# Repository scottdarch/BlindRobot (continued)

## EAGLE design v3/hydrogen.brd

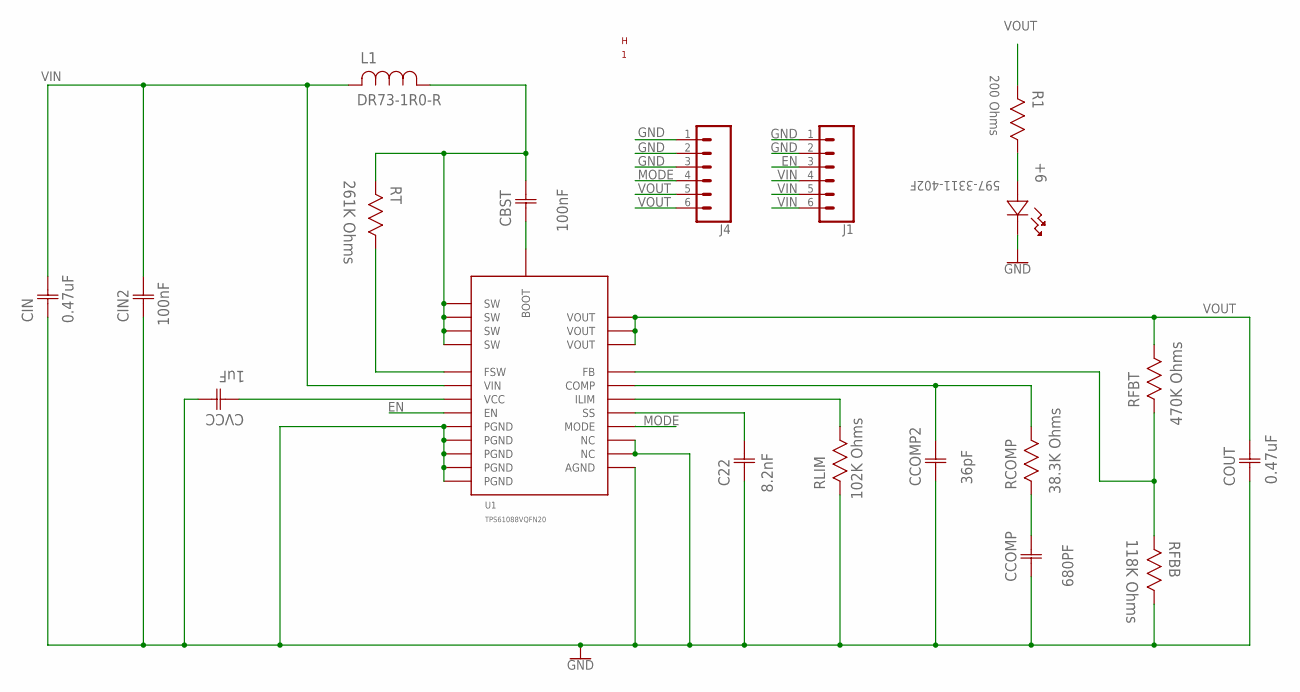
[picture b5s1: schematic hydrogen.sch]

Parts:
+6: 597-3311-402F; LED_597-3311-402F
C22: 8.2nF; CAPC1005X60N
CBST: 100nF; CAPC2013X94N
CCOMP: 680PF; CAPC1608X90N
CCOMP2: 36pF; CAPC1005X60N
CIN: 0.47uF; CAPC3216X180N
CIN2: 100nF; CAPC1005X60N
COUT: 0.47uF; CAPC3216X180N
CVCC: 1uF; CAPC1608X85N
H: 1; PERIODIC_SYMBOL_BACK
J1, J4: CONN_06LONGPADS; 1X06_LONGPADS
L1: DR73-1R0-R; INDM7676X355N
R1: 200 Ohms; RESC3216X71N
RCOMP: 38.3K Ohms; RESC1005X40N
RFBB: 118K Ohms; RESC1005X40N
RFBT: 470K Ohms; RESC1608X60N
RLIM: 102K Ohms; RESC1005X40N
RT: 261K Ohms; RESC1005X40N
U1: TPS61088VQFN20; VQFN20

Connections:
BOOT: CBST.1 (C1), U1.P$8 (BOOT)
COMP: CCOMP2.2 (C2), RCOMP.1, U1.P$18 (COMP)
EN: J1.3, U1.P$2 (EN)
FB: RFBB.2, RFBT.2 (R2), U1.P$17 (FB)
FSW: RT.1, U1.P$3 (FSW)
GND: +6.1, C22.1 (C1), CCOMP.1 (C1), CCOMP2.1 (C1), CIN.1 (C1), CIN2.1 (C1), COUT.1 (C1), CVCC.2 (C2), J1.1 (>NAME), J1.2, J4.1 (>NAME), J4.2, J4.3, RFBB.1, RLIM.2, U1.P$11 (NC), U1.P$12 (NC), U1.P$20 (AGND), U1.P$21 (PGND), U1.P$22 (PGND), U1.P$23 (PGND), U1.P$24 (PGND), U1.P$25 (PGND)
ILIM: RLIM.1, U1.P$19 (ILIM)
LED_ANODE: +6.2, R1.1
MODE: J4.4, U1.P$13 (MODE)
unnamed: CCOMP.2 (C2), RCOMP.2
SS: C22.2 (C2), U1.P$10 (SS)
SW: CBST.2 (C2), L1.1, RT.2, U1.P$4 (SW), U1.P$5 (SW), U1.P$6 (SW), U1.P$7 (SW)
VCC: CVCC.1 (C1), U1.P$1 (VCC)
VIN: CIN.2 (C2), CIN2.2 (C2), J1.4, J1.5, J1.6, L1.2, U1.P$9 (VIN)
VOUT: COUT.2 (C2), J4.5, J4.6, R1.2, RFBT.1 (R1), U1.P$14 (VOUT), U1.P$15 (VOUT), U1.P$16 (VOUT)

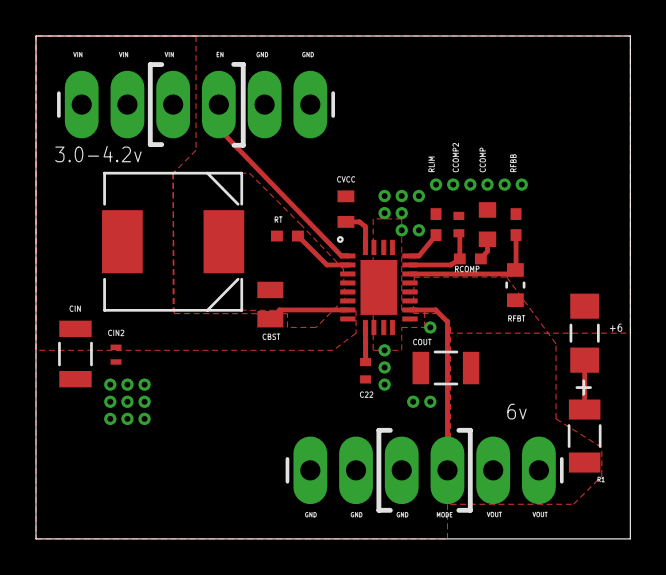
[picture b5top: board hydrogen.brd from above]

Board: 2 copper layers, 33.0 x 27.9 mm, 20 parts (0 on the bottom side), 15 nets.

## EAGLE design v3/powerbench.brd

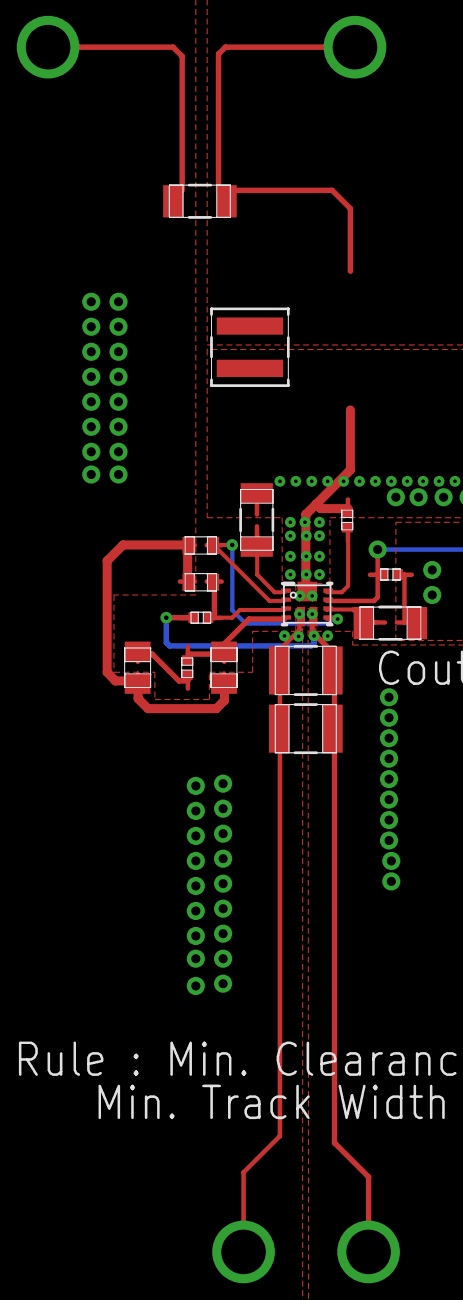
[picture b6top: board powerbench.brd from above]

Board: 4 copper layers, 19 parts (0 on the bottom side), 11 nets.

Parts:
Cbst: 0402
Ccomp, Ccomp2: 0805
Cin: 1206_190
Cin2: 0402
Cout_1, Cout_2: 1210_280
Cvcc: 0603
GND, GND1: TP-1502
L1: XAL4020
Rcomp: 0402
Rfbb: 0603
Rfbt: 0402
Rlim: 1206
Rt: 1206
U1: RNR0011A
VIN: TP-1502
VOUT: TP-1502

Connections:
0: Ccomp.2, Ccomp2.2, Cin.2, Cin2.2, Cout_1.2, Cout_2.2, Cvcc.2, GND.1, GND1.1, Rfbb.2, Rlim.2, U1.5
2: Ccomp2.1, Rcomp.1, U1.4
3: Cin.1, Cin2.1, L1.1, U1.9, VIN.1
4: Cout_1.1, Cout_2.1, Rfbt.1, U1.6, VOUT.1
6: Rfbb.1, Rfbt.2, U1.3
7: Cbst.2, L1.2, Rt.1, U1.11
8: Rt.2, U1.1
9: Ccomp.1, Rcomp.2
11: Rlim.1, U1.8
13: Cbst.1, U1.10
15: Cvcc.1, U1.2, U1.7

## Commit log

2016-03-17 Starting a little robot project.
2016-03-17 Adding Yakindu model.
2016-03-18 Progress on bare-metal build
2016-03-18 Adding the Arduino Zero linker script.
    Using the Arduino script as a starting point.
2016-03-18 Compiles with ASF/CMSIS
2016-03-19 Adding size target and some cleanup.
2016-03-19 Adding automatic dependency handling.
2016-03-19 Adding openocd programming support.
2016-03-19 Getting eclipse CDT to work (woot!)
2016-03-20 Progress on ASF integration.
    Moveing to board oriented configuration.
    This change doesn't build yet but it's close.
2016-03-20 Fixing build.
    This looks like it's good to go with ASF development.
2016-03-21 Blinky works!
2016-05-19 Cleaning up makefile a bit.
    Also adding atmega board
2016-05-21 Setting up arduino pro as motor controller.
2017-01-14 Don't know. Doing a reset.
2017-01-14 Doing a reset of this project.
2017-01-15 Starting to build infineon HBridge board
2017-01-15 First working build.
    Flashing not tested yet.
2017-01-15 Got jlink flashing working.
2017-01-15 Adding H-Bridge 2 go samples.
2017-01-16 Making motor_control into a simple blinky.
2017-01-16 Prettier der blikenlight.
2017-02-28 Starting on v3 motor control board.
2017-03-01 Adding progress on designing powerboard.
2017-03-03 Progress on two-rail power supply.
2017-03-03 Ignoring EAGLE lck files.
2017-03-03 6v schematic complete.
2017-03-04 Progress on 6v eval board.
2017-03-04 Significant progress on layout for 6v eval.
    TODO:
    * bottom layer
    * vias
    * DRC errors in QFN part.
2017-03-05 Hydrogen board v1r0 off to OSH park.
2017-03-05 Helium board off to OSH park!
    Woot!
2017-03-05 Small tweaks. Not board spin.
2017-03-07 Start of lithium board.
2017-03-09 Significant completion of scheamtic.
2017-03-12 Lego module mechanical and 5v rail
    Switching to a 5v supply from the 3.3. Will use an LDO on the motor board to get 3.3. from the 5.
    In-general, committing to a BB green/ROS controller for this robot.
2017-03-16 Progress on Lithium board.
2017-03-17 Significant completion of Lithium layout.
    TODO:
    1. reverse voltage protection.
    2. silk screen
2017-03-18 Moving away from bb ideas.
2017-03-19 New lithium mechanically complete.
2017-03-20 Lithium with ATTiny84 for ADC.
2017-03-21 Lithium schematic complete.
2017-03-21 Small fixes to ATTiny84 package.
2017-03-23 Major layout completion.
    Still need some via stitching of gnd and silkscreen.
2017-03-24 Okay, I think this fixed it.
2017-03-24 Release candidate.
2017-03-25 Seed order 170325111000
2017-03-25 Stubbing out Beryllium board.
2017-03-28 Some small, post-rev0 tweaks.
2017-03-28 Reset for v3 design.
    Moving away from infineon m0.
2017-04-03 Setting up Lithium firmware.
2017-04-03 Moving a via away from the ISP pads.
2017-04-03 Stubbing out ESC build.
2017-04-03 Hooking up openOCD to makefile.
2017-04-06 Some cleanup of Lithium layout and repo files.
2017-04-07 Parking forward progress. Trying Atmel start for i2c
2017-04-07 Fixing assembly build in Makefile.
2017-04-08 Lots of fixes in the makefile but still not working?
2017-04-08 Still no worky?
2017-04-08 Resync ASF from AS7.0
2017-04-08 Adding JLink loadfile script.
2017-04-08 Friggen fixing it. ARGHAHHHHH!
2017-04-09 Stubbing out Attiny firmware
    Also enabling debugwire via AVR Dragon.
2017-04-09 Integrating with Yakindu
2017-04-09 Backing out Yakindu. Headless is non-functional.
2017-04-10 Progress on USI peripheral using Yakiundu Community.
2017-04-12 Progress on TWI statemachine.
2017-04-13 TWI seems to be working on some level. Just need to debug
2017-04-15 Working I2C demo.
    Sleep mode not working. Need to investigate this.
2017-04-15 Fixing sleep.
    Was sleeping within ISR. Whoops.
2017-04-15 I2C statemachine complete.
    Still need to get the general driver protocol defined and implemented.
2017-04-16 Progress on network layer for SMB
2017-04-17 Starting Boron evaluation of bq24160
2017-04-19 Progress on Boron eval board.
2017-04-20 Schematic Complete.
    Unless I go with a different 5V supply.
2017-04-21 Good progress on Boron layout.
2017-04-23 Boron off to OSH.
2017-04-23 Boron R0 send to OSH part + NOTIFY.
2017-04-24 Boron r.1 off to OSH park.
2017-04-24 Fixing the stupid backwards USB port.
    Doh!
2017-04-25 Boron R.3 off to osh park.
2017-04-30 Progress on the ATTiny I2C driver.
2017-05-01 General progress on the power monitor firmware.
2017-05-14 Renaming offensive I2C slave to subordinate.
2017-05-14 Stubbing out I2C master driver.
2017-05-14 Rough out TWI master from Atmel sample.
    AppNote: AVR310 - Using the USI module as a TWI Master
2017-05-15 Verified I2C. Master driver still incomplete.
2017-05-27 Starting Rev 2 of Lithium.
2017-05-28 Crappy firmware to init for 3.7v.
2017-05-30 Allowing 2.5A charging.
2017-06-24 Progress on Lithium rev 2
2017-07-16 Starting controls development using Zumo
    https://www.pololu.com/product/2510
2017-07-17 Rough-out of stateful robot firmware.
2017-07-28 Playing with Zumo bot.
2017-07-31 Progress on Encoder class for Arduino Zero.
2017-08-06 Designing FIR filter for encoder input.
2017-08-06 Adding unfiltered rendering.
2017-08-06 Moving BokehJS inline.
2017-08-06 Trying MatPlotLib on github.
2017-08-06 Replacing Bokeh with Matplotlib.
    Now renders on GitHub!
2017-08-07 Adding scope trace of data.
2017-08-07 Adding integration as sanity check.
2017-08-14 Adding phase classifiers to encoder events.
2017-12-31 Some random changes.
